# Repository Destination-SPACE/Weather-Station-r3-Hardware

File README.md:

# Weather-Station-r3
Destination Weather Station R3 Hardware

# License
Licensed under the CERN OHLv2 - [Permissive](https://github.com/Destination-SPACE/Weather-Station-r3-Hardware/blob/main/LICENSE) or as referenced

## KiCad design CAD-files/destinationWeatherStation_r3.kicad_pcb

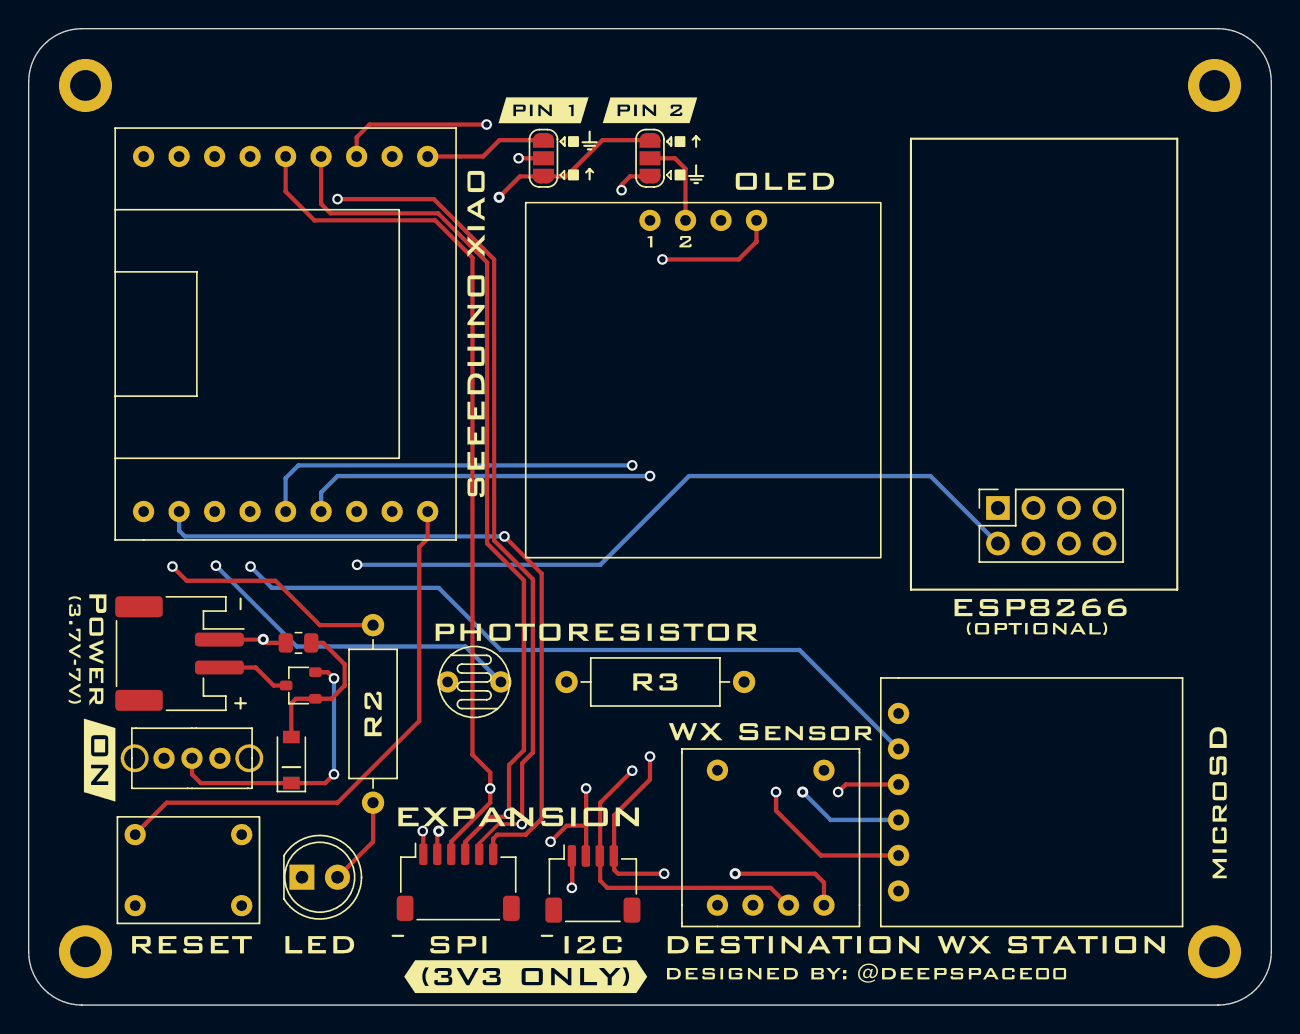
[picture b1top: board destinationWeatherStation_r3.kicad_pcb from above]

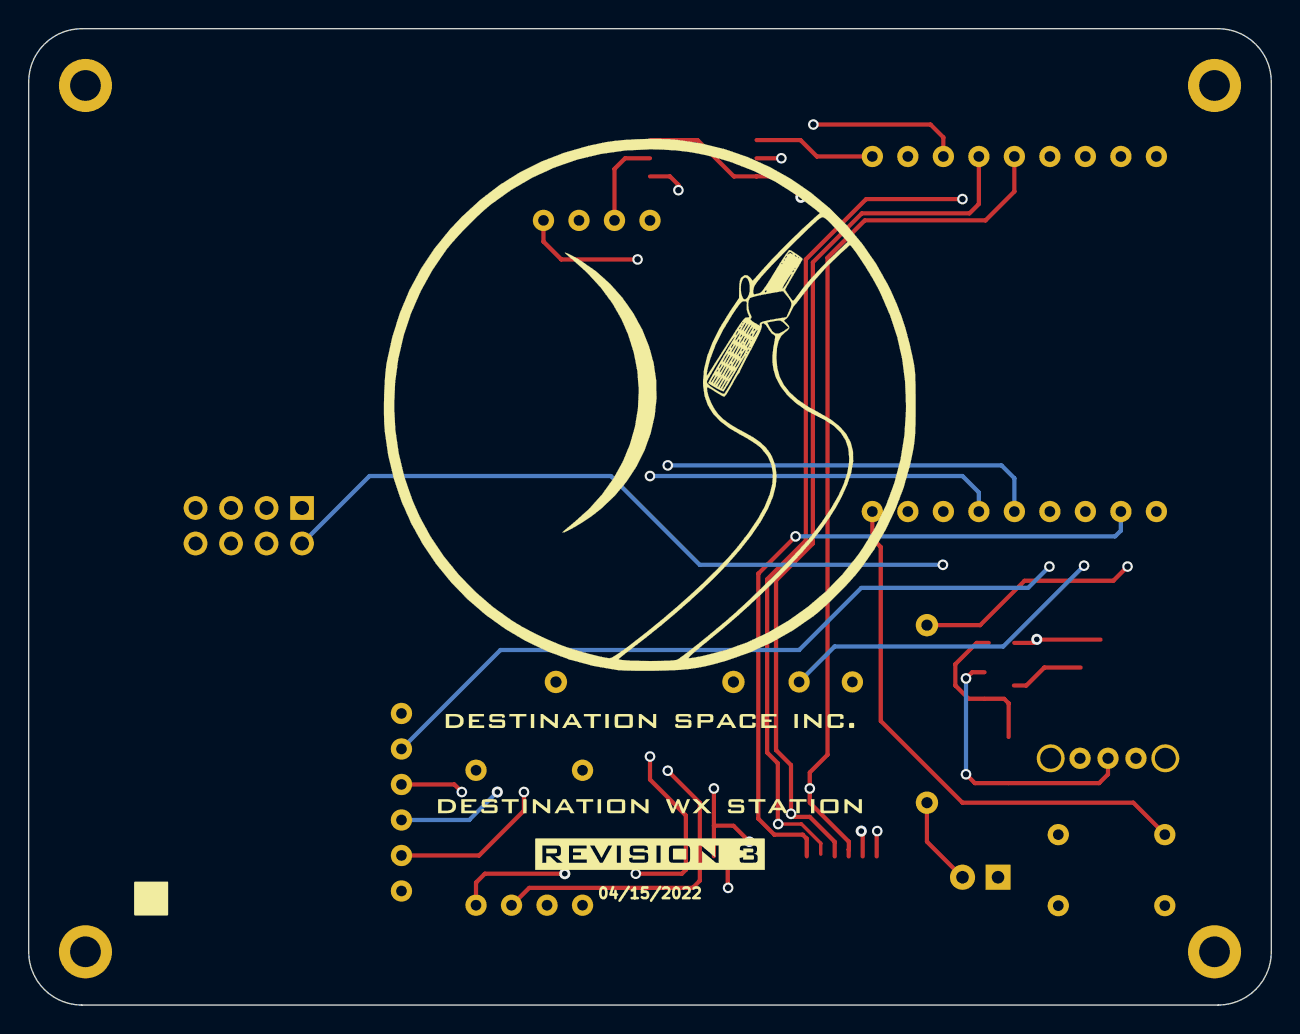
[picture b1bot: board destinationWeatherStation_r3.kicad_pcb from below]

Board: 4 copper layers, 88.9 x 69.8 mm, 46 parts (3 on the bottom side), 21 nets.

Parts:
D1: MMSZ5235B; D_SOD-123
D2: LED; LED_D5.0mm
J1: Conn_01x02_Female; JST_PH_S2B-PH-SM4-TB_1x02-1MP_P2.00mm_Horizontal
J2: Conn_02x04_Odd_Even; PinHeader_2x04_P2.54mm_Vertical
J3: Conn_01x04_Female; JST_SH_SM04B-SRSS-TB_1x04-1MP_P1.00mm_Horizontal
J4: Conn_01x06_Female; JST_SH_SM06B-SRSS-TB_1x06-1MP_P1.00mm_Horizontal
JP1, JP2: Jumper_3_Open; SolderJumper-3_P1.3mm_Open_RoundedPad1.0x1.5mm
Q1: RRR040P03HZG; SC-96
R1: 100R; R_0805_2012Metric
R2: R_Small_US; R_Axial_DIN0309_L9.0mm_D3.2mm_P12.70mm_Horizontal
R3: 10K; R_Axial_DIN0309_L9.0mm_D3.2mm_P12.70mm_Horizontal
R4: R_Photo; photoresistor
SW1: SW_SPDT
SW2: SW_Push_Dual; DPDTPushButton
U1: XiaoCarrier
U2: OLED_module
U3: BME280Breakout
U4: SD-module; SDModule
kibuzzard-6212B2ED: G***; kibuzzard-6212B2ED
kibuzzard-62111A8A: G***; kibuzzard-62111A8A
kibuzzard-62111A14: G***; kibuzzard-62111A14
kibuzzard-62111A45: G***; kibuzzard-62111A45
kibuzzard-62111ABC: G***; kibuzzard-62111ABC
kibuzzard-62111B43: G***; kibuzzard-62111B43
kibuzzard-62155D2C: G***; kibuzzard-62155D2C
kibuzzard-62598C40: G***; kibuzzard-62598C40
kibuzzard-621113A9: G***; kibuzzard-621113A9
kibuzzard-621113E9: G***; kibuzzard-621113E9
kibuzzard-621114C2: G***; kibuzzard-621114C2
kibuzzard-6211110C: G***; kibuzzard-6211110C
kibuzzard-6211115D: G***; kibuzzard-6211115D
kibuzzard-6211129D: G***; kibuzzard-6211129D
kibuzzard-6211136D: G***; kibuzzard-6211136D
kibuzzard-6211140D: G***; kibuzzard-6211140D
kibuzzard-6211193D: G***; kibuzzard-6211193D
kibuzzard-62111182: G***; kibuzzard-62111182
kibuzzard-62111204: G***; kibuzzard-62111204
kibuzzard-62111233: G***; kibuzzard-62111233
kibuzzard-62111258: G***; kibuzzard-62111258
kibuzzard-62111327: G***; kibuzzard-62111327
kibuzzard-62111432: G***; kibuzzard-62111432
kibuzzard-62111477: G***; kibuzzard-62111477
kibuzzard-62111924: G***; kibuzzard-62111924
kibuzzard-62111949: G***; kibuzzard-62111949
kibuzzard-62360720: G***; kibuzzard-62360720

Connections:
+3V3: J2.4, J2.8, J3.2, J4.2, JP1.1 (A), JP2.3 (B), R4.1, U1.3 (+3V3), U3.2 (+3V3), U4.1 (3V3)
A2: R3.1, R4.2, U1.16 (A2)
D0: R2.1, U1.18 (A0)
D1: J4.6, U1.17 (A1)
D3: U1.15 (A3), U4.2 (CS)
GND: D2.1 (K), J1.1, J2.1, J3.1, J4.1, JP1.3 (B), JP2.1 (A), R1.2, R3.2, SW2.3, U1.2 (GND), U1.9 (GND), U3.1 (GND), U3.5 (GND), U3.6 (GND), U4.6 (GND)
MISO: J4.3, U1.5 (MISO), U4.5 (MISO)
MOSI: J4.5, U1.4 (MOSI), U4.3 (MOSI)
unnamed: D1.1 (K), Q1.2 (S), SW1.2 (B)
unnamed: D1.2 (A), Q1.1 (G), R1.1
unnamed: D2.2 (A), R2.2
unnamed: J1.2, Q1.3 (D)
unnamed: JP1.2 (C), U2.1 (VCC)
unnamed: JP2.2 (C), U2.2 (GND)
RST: SW2.1, U1.10 (~RESET)
RX: J2.7, U1.7 (RX)
SCK: J4.4, U1.6 (SCK), U4.4 (CLK)
SCL: J3.4, U1.13 (SCL), U2.3 (SCL), U3.4 (SCL)
SDA: J3.3, U1.14 (SDA), U2.4 (SDA), U3.3 (SDA)
TX: J2.2, U1.12 (TX)
VCC: SW1.1 (A), U1.1 (5V)

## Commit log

2021-08-23 Added CERN OHL
2021-09-06 updated OHL

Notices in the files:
CAD-files/destinationWeatherStation_r3.kicad_pcb:
Licensed under CERN OHLv2 - Permissive
